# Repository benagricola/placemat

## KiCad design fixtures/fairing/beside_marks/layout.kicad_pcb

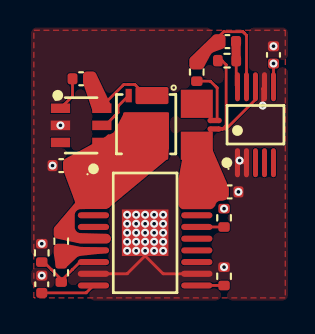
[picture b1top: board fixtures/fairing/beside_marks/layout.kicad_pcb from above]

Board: 6 copper layers, 20 parts (0 on the bottom side), 17 nets.

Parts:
C1: CL05B103KB5NNNC; C_0402_1005Metric
C2, C3, C4, C5, C6: CL05B104KB54PNC; C_0402_1005Metric
NT1, NT2: NetTie-2_SMD_Pad0.3mm
R1, R7: ERJ-2RKF1003X; R_0402_1005Metric
R2: ERJ-2RKF2003X; R_0402_1005Metric
R3: AC0402FR-071M2L; R_0402_1005Metric
R4: ERJ-2RKF4701X; R_0402_1005Metric
R5, R6: ERJ-2RKF10R0X; R_0402_1005Metric
R8: PE1206DRM470R01L; PE1206_Yageo_Table8
U1: TPS16630PWPR; HTSSOP-20_L6.5-W4.4-P0.65-LS6.4-TL-EP2.58
U2: INA226AIDGSR; MSOP-10_L3.0-W3.0-P0.50-LS5.0-BL
U3: MDDG06R10Q; DFN-8_L3.3-W3.3-P0.65-BL
U4: LM74700QDBVRQ1; SOT-23-6_L2.9-W1.6-P0.95-LS2.8-TL

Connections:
DVDT_SET: C1.1, U1.10
GND: C1.2, C3.2, C5.2, C6.2, R1.2, R4.2, U1.9, U1.12, U1.21, U2.1, U2.2, U2.7, U4.2
ILIM_SET: R4.1, U1.11
INA_N: C2.2, R5.2, U2.9
INA_P: C2.1, R6.2, U2.10
OVP_SET: R1.1, R2.2, U1.8
PGOOD: R7.2, U1.16
REV_CAP: C4.1, U4.1
REV_GATE: U3.4, U4.5
UVLO_SET: R2.1, R3.2, U1.7
V3V3: C3.1, R7.1, U2.6
VBIKE: C4.2, U3.1, U3.2, U3.3, U4.6
VPROT: C5.1, NT1.1, R8.1, U1.18, U1.19, U1.20
VPROT_IN: C6.1, R3.1, U1.1, U1.2, U1.3, U1.6, U3.5, U4.4
VPROT_SENSE: NT1.2, R6.1, U2.8
VSHUNT: NT2.1, R8.2
VSHUNT_SENSE: NT2.2, R5.1

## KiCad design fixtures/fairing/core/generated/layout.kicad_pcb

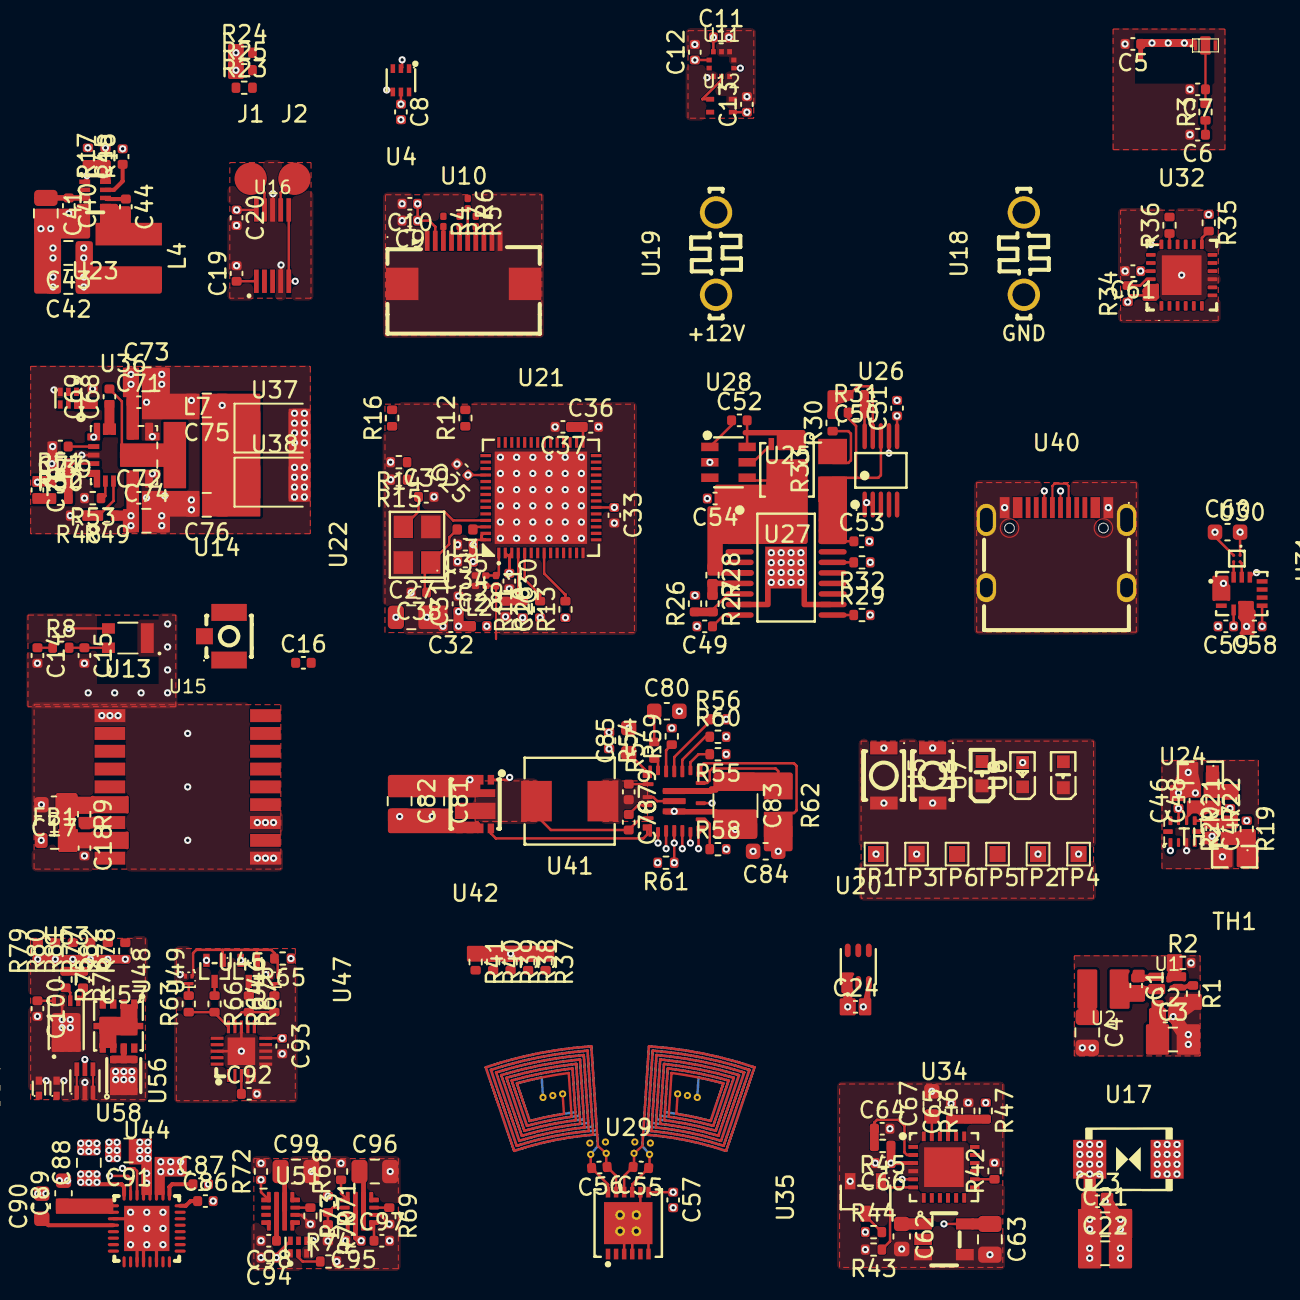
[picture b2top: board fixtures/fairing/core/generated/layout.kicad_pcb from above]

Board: 6 copper layers, 258 parts (0 on the bottom side), 154 nets.

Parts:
C1, C2, C8, C9, C11, C12, C13, C16, C18, C23, C25, C30, C32, C33, C37, C40, C44, C46, C47, C48, C50, C51, C52, C53, C54, C58, C59, C61, C65, C66, C68, C69, C71, C72, C78, C79, C92, C93, C94, C95, C98, C100: CL05B104KB54PNC; C_0402_1005Metric
C3, C4, C21, C22, C27, C41, C63, C81, C82, C88, C91: GRM21BR61H106KE43L; C_0805_2012Metric
C5, C6, C7: GRM1555C1H1R0BA01D; C_0402_1005Metric
C10, C24, C26, C31, C34, C36, C57, C77: CL05A105KA5NQNC; C_0402_1005Metric
C14, C15: GCM1555C1H100FA16D; C_0402_1005Metric
C17, C85, C89, C90: CL10A106MA8NRNC; C_0603_1608Metric
C19, C20: KAM05CR71A105MH; C_0402_1005Metric
C28, C29: GRM0335C1H1R5CA01D; C_0201_0603Metric
C35, C49, C64, C97: CL05B103KB5NNNC; C_0402_1005Metric
C38, C39: GCM1555C1H160FA16D; C_0402_1005Metric
C42, C43, C75, C76: GRM21BZ71A226ME15L; C_0805_2012Metric
C45: GRM155R71H333KE14D; C_0402_1005Metric
C55, C56, C86, C87: CL05C331JB5NNNC; C_0402_1005Metric
C60, C84: GRM188R61E475KE11D; C_0603_1608Metric
C62: CL10A105KB8NNNC; C_0603_1608Metric
C67: CL10B474KA8NNNC; C_0603_1608Metric
C70: GCM1555C1H220FA16D; C_0402_1005Metric
C73, C74: CL21A475KBQNNNE; C_0805_2012Metric
C80: 0603B222K500NT; C_0603_1608Metric
C83: GMK325BJ226MM-T; C_1210_3225Metric
C96, C99: CL21A225KBQNNNE; C_0805_2012Metric
FB1: BLM18EG601SZ1D; R_0603_1608Metric
J1, J2: YTC1P-3515-01; TESTPOINT-SMD_BD2.0_pitch2.7
L1: 2.4nH; L_0201_0603Metric
L2: LQG15HS2N0S02D; L_0402_1005Metric
L3: 24nH; L_0402_1005Metric
L4: APH404012C2R2MP01; APH404012_APV_land
L5: PCB sector coil V3; RingCoil_V3_M
L6: PCB sector coil V3; RingCoil_V3
L7: APH404012C1R5MP01; APH404012_APV_land
R1, R24, R25, R29, R40, R41: ERJ-2RKF4701X; R_0402_1005Metric
R2: WR04W2R00FTL; R_0402_1005Metric
R3, R8, R9, R54, R60: ERJ-2GE0R00X; R_0402_1005Metric
R4, R5, R6, R7: RC0201FR-0733RL; R_0201_0603Metric
R10, R11, R13, R14, R15, R17, R23, R34, R35, R37, R57, R58, R75, R76, R77, R78, R79, R80, R81, R82: 0402WGF1002TCE; R_0402_1005Metric
R12: ERJ-2RKF1000X; R_0402_1005Metric
R16: 0402WGF5100TCE; R_0402_1005Metric
R18: ERJ-2RKF3162X; R_0402_1005Metric
R19, R21, R45: ERJ-2RKF4702X; R_0402_1005Metric
R20, R22, R36, R52: ERJ-2RKF1001X; R_0402_1005Metric
R26, R32, R38, R39, R42, R46, R49, R55, R56, R61, R65, R66, R67, R68, R70, R72, R74: ERJ-2RKF1003X; R_0402_1005Metric
R27: ERJ-2RKF2003X; R_0402_1005Metric
R28: AC0402FR-071M2L; R_0402_1005Metric
R30, R31: ERJ-2RKF10R0X; R_0402_1005Metric
R33, R62: PE1206DRM470R01L; PE1206_Yageo_Table8
R43, R44, R47, R63, R64: ERJ-2RKF1004X; R_0402_1005Metric
R48: ERJ-2RKF2212X; R_0402_1005Metric
R50: RT0402BRD0716K9L; R_0402_1005Metric
R51: RT0402BRD0769K8L; R_0402_1005Metric
R53: ERJ-2RKF5761X; R_0402_1005Metric
R59: ERJ-2RKF5102X; R_0402_1005Metric
R69: ERJ-2RKF6651X; R_0402_1005Metric
R71: 400k; R_0402_1005Metric
R73: ERJ-2RKF9760X; R_0402_1005Metric
TH1, TH2: NCU18XH103F60RB; R0603
TP1, TP2, TP3, TP4, TP5, TP6: ?; TestPoint_Pad_1.0x1.0mm
U1: TPS92200D2RXLR; RXL0006A_TI_land
U2: DFE252012F-2R2M=P2; DFE252012F_Murata_land
U3: ANT016008LCS2442MA1; ANT-SMD_6P-L1.6-W0.8-P1.20-1
U4: TMP102AIDRLR(UMW); SOT-563_L1.6-W1.2-P0.50-LS1.6-BL
U5: KT-0603R; LED-SMD_L1.6-W0.8-R-RD
U6: KT-0603W; LED0603-R-RD_WHITE
U7: KT-0603YG; LED0603-RD
U8, U9: B3U-1000P; KEY-SMD_B3U-1000PM
U10: 05A20L10P; FPC-SMD_10P-P0.50_05A20L10P
U11: BMP581; BMP581_Bosch_land
U12: SHT40-AD1B-R3; SHT40_Sensirion_land
U13: W3011; ANT-W3011_DATASHEET
U14: BWU.FL-IPEX1; IPEX-SMD_BWIPX-1-001E
U15: MAX-M10S-00B; GNSS_LCC18_shared_land
U16: DRV2605LDGSR; DGS0010A_TI_land
U17: SMBJ26CA; SMB_L4.6-W3.6-LS5.3-BI
U18, U19: 1217169-1; TH-2P_L7.9-W0.80-P5.08
U20: LTR-303ALS-01; TDFN-6_L2.0-W2.0-P0.65-BL
U21: ESP32-S3FH4R2; QFN-56_L7.0-W7.0-P0.40-BL-EP5.7
U22: S3240000101040; CRYSTAL-SMD_4P-L3_2-W2_5-BL
U23: TPS62933DRLR; SOT-583-8_L2.1-W1.2-P0.50-LS1.6-BR
U24: ADS1115IRUGR; ADS1115_RUG0010A
U25: TPS16630PWPR; HTSSOP-20_L6.5-W4.4-P0.65-LS6.4-TL-EP2.58
U26: INA226AIDGSR; MSOP-10_L3.0-W3.0-P0.50-LS5.0-BL
U27: MDDG06R10Q; DFN-8_L3.3-W3.3-P0.65-BL
U28: LM74700QDBVRQ1; SOT-23-6_L2.9-W1.6-P0.95-LS2.8-TL
U29: LDC1612DNTR; WSON-12_L4_0-W4_0-P0_50-BL-EP
U30: LSM6DS3TR-C; LGA-14_L3.0-W2.5-P0.50-TL
U31: MMC5603NJ; FLIPCHIP-4_L0.8-W0.8-R2-C2-P0.40-TL
U32: TCA9555RTWR; VFQFPN-24_L4.0-W4.0-P0.50-BL-EP2.8
U33: TPS7B6933DBVR; TSOT-23-5_L2.9-W1.6-P0.95-LS2.8-BR
U34: MSPM0L1106TRGER; VQFN-24_L4.0-W4.0-P0.50-TL-EP2.5
U35: 2N7002; SOT-23-3_L2.9-W1.3-P1.90-LS2.4-BR
U36: LM61440AASQRJRRQ1; VQFN-14_L4.0-W3.5-P0.5-BL-RJR0014A
U37, U38: T520T107M006APE070; CP_EIA-3528-12_Kemet-T
U39: SN74LVC1G07DRYR(UMW); SON-6_L1.5-W1.0-P0.50-BL
U40: TYPE-C-31-M-12; TYPE-C-31-M-12-corrected-power-lands
U41: MWSA0518S-2R2MT; IND-SMD_L5.4-W5.2
U42: AON7934; DFN-8_L3.0-W3.0-P0.65-BL_AON7934
U43: TPS55288RPMR; RPM0026A
U44: TPS25751SRSMR; QFN-32_L4.0-W4.0-P0.40-TL-EP2.8
U45: TPD6S300RUKR; WQFN-20_L3.0-W3.0-P0.40-BL-EP1.7
U46, U47: CSD15380F3; PICOSTAR-3_L0.7-W0.6-P0.35-TL
U48, U49: DMG1013T-7; SC-75-3_L1.6-W0.8-P1.00-LS1.6-BR
U50, U52: TPS259470LRPWR; RPW0010A
U51: SN74LVC1G08DRYR; SON-6_L1.5-W1.0-P0.50-BL
U53: M24512-DFMC6TG; DFN-8_L3.0-W2.0-P0.50-BL-EP
U54, U55: ESD9B5.0ST5G; SOD-923_L0.8-W0.6-LS1.0-BI
U56: USBLC6-2P6; SOT-666-6_L1.6-W1.2-P0.50-LS1.6-BR
U57: TVS2200DRVR; WSON-6_L2.0-W2.0-P0.65-BL-EP
U58: AON7804; DFN-8_L3.0-W3.0-P0.65-BL_AON7804-1

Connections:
ALS_INT: R37.2, U20.5, U32.14
BB_FAULT: R35.2, R55.2, U32.13, U43.14
BL_LEDK: R2.1, U1.6, U10.9
BL_PWM: R1.1, U1.5, U21.10
BOOT_STRAP: R10.2, TP2.1, U8.1, U21.5
DISP_CS: R4.1, U21.17
DISP_DC: R5.1, U21.22
DISP_MOSI: R6.1, U21.21
DISP_RST: U10.4, U21.18
DISP_SCK: R7.1, U21.19
DISP_TE: U10.8, U21.23
EFUSE_SHDN: U25.13, U34.5
GND: C2.2, C3.2, C4.2, C5.2, C6.2, C7.2, C8.2, C9.2, C10.2, C11.2, C12.2, C13.2, C14.2, C15.2, C16.2, C17.2, C18.2, C19.2, C20.2, C21.2, C22.2, C23.2, C24.2, C25.2, C26.2, C27.2, C28.2, C29.2, C30.2, C31.2, C32.2, C33.2, C34.2, C35.2, C36.2, C37.2, C38.2, C39.2, C40.2, C41.2, C42.2, C43.2, C45.2, C46.2, C47.2, C48.2, C49.2, C51.2, C53.2, C54.2, C57.2, C58.2, C59.2, C60.2, C61.2, C62.2, C63.2, C64.2, C65.2, C66.2, C67.2, C69.2, C71.2, C72.2, C73.2, C74.2, C75.2, C76.2, C77.2, C81.2, C82.2, C83.2, C84.2, C86.2, C87.2, C88.2, C89.2, C90.2, C91.2, C92.2, C93.2, C94.2, C95.2, C96.2, C97.2, C98.2, C99.2, C100.2, R1.2, R2.2, R14.2, R15.2, R17.2, R26.2, R29.2, R42.2, R43.2, R46.2, R48.2, R50.2, R53.2, R54.2, R58.2, R61.2, R68.2, R69.2, R70.2, R72.2, R73.2, R74.2, TH1.2, TH2.2, TP3.1, U1.4, U3.4, U4.2, U4.4, U5.2, U6.2, U8.2, U9.2, U10.10, U10.11, U10.12, U11.3, U11.5, U11.7, U11.8, U11.9, U12.4, U13.2, U14.2, U14.3, U15.1, U15.10, U15.12, U16.4, U16.8, U17.2, U18.1, U18.2, U20.3, U21.57, U22.2, U22.4, U23.1, U23.4, U24.3, U25.9, U25.12, U25.21, U26.1, U26.2, U26.7, U28.2, U29.3, U29.4, U29.6, U29.8, U29.13, U30.1, U30.2, U30.3, U30.6, U30.7, U31.A1, U32.9, U32.25, U33.3, U33.4, U34.4, U34.25, U35.2, U36.3, U36.9, U36.11, U37.2, U38.2, U39.3, U40.1, U40.2, U40.3, U40.4, U40.A1B12, U40.B1A12, U42.5, U42.6, U42.7, U43.7, U43.9, U43.24, U44.3, U44.11, U44.12, U44.14, U44.33, U45.4, U45.5, U45.6, U45.7, U45.8, U45.13, U45.18, U45.21, U46.2, U47.2, U50.8, U51.3, U52.8, U53.1, U53.2, U53.3, U53.4, U53.7, U53.9, U54.2, U55.2, U56.2, U57.1, U57.2, U57.3, U57.7
GNSS_PPS: U15.4, U21.9
GNSS_RX: U15.3, U21.7
GNSS_TX: U15.2, U21.6
IMU_INT1: U21.27, U30.4
INA_ALERT: R34.2, R38.2, U21.12, U26.3, U32.22
LED_BIKE: R23.2, U5.1
LED_STATUS: R12.2, U6.1
LED_USB_K: R36.2, U7.1
MCU_EN: C26.1, R11.2, TP4.1, U9.1, U21.4
PD_IRQ: R78.2, U21.47, U44.10
PD_NEGOTIATING: R77.2, U21.44, U44.13
PD_PDO0: R79.2, U21.11, U44.6
PD_PDO1: R80.2, U21.16, U44.7
PD_PDO2: R81.2, U21.24, U44.18
PGOOD: R32.2, U25.16, U32.12
PP5V: C70.1, C75.1, C76.1, C91.1, L7.2, R51.1, U36.1, U37.1, U38.1, U44.28, U44.29
RAIL_FAULT: R39.2, U25.15, U32.15
REV_EN: R44.2, U28.3, U35.3
RF_50: C6.1, C28.1, L1.2, R3.1
RING_INT: U21.15, U29.5
SCL: R40.2, U11.2, U12.2, U16.2, U20.4, U21.14, U29.1, U30.13, U31.A2, U34.1
SCL_PWR: R24.2, U4.1, U21.37, U24.10, U26.5, U32.19, U43.5, U44.9
SDA: R41.2, U11.4, U12.1, U16.3, U20.6, U21.13, U29.2, U30.14, U31.B2, U34.24
SDA_PWR: R25.2, U4.6, U21.48, U24.9, U26.4, U32.20, U43.6, U44.8
UART_RX: TP5.1, U21.50
UART_TX: R16.2, TP6.1
USB_CC1: C86.1, U40.A5, U44.24, U54.1
USB_CC2: C87.1, U40.B5, U44.25, U55.1
USB_D_N: U21.25, U40.A7, U40.B7, U56.3, U56.4
USB_D_P: U21.26, U40.A6, U40.B6, U56.1, U56.6
USB_HV: C84.1, C98.1, R62.2, U43.13, U52.5
USB_SBU1: U40.A8, U45.1
USB_SBU2: U40.B8, U45.2
USB_WET: R82.2, U21.45, U44.30, U52.2
V3V3: C8.1, C9.1, C10.1, C11.1, C12.1, C13.1, C20.1, C24.1, C25.1, C27.1, C31.1, C32.1, C33.1, C34.1, C35.1, C42.1, C43.1, C46.1, C51.1, C57.1, C58.1, C59.1, C60.1, C61.1, C69.1, C88.1, C94.1, FB1.1, L2.1, L4.2, R10.1, R11.1, R13.1, R18.1, R19.1, R21.1, R24.1, R25.1, R32.1, R34.1, R35.1, R37.1, R38.1, R39.1, R40.1, R41.1, R55.1, R77.1, R78.1, R79.1, R80.1, R81.1, R82.1, TP1.1, U4.5, U7.2, U10.2, U11.1, U11.6, U11.10, U12.3, U16.5, U16.6, U16.10, U20.1, U21.20, U21.46, U21.55, U21.56, U24.1, U24.8, U26.6, U29.7, U30.5, U30.8, U30.12, U31.B1, U32.18, U32.21, U32.23, U32.24, U39.6, U44.32, U51.6, U56.5
VBIKE: C21.1, C22.1, C23.1, C52.2, R44.1, R47.1, U17.1, U19.1, U19.2, U27.1, U27.2, U27.3, U28.6
VBUS: C99.1, U40.A4B9, U40.B4A9, U44.26, U44.27, U52.6, U57.4, U57.5, U57.6, U58.5
VBUS_EN: R61.1, U21.36, U39.2, U43.4, U51.1
VLED: C4.1, U2.2, U10.1
VPROT_IN: C54.1, C62.1, R28.1, U25.1, U25.2, U25.3, U25.6, U27.5, U28.4, U33.1
VSHUNT: C2.1, C3.1, C40.1, C41.1, C71.1, C72.1, C73.1, C74.1, C81.1, C82.1, C96.1, R23.1, R30.1, R33.2, R49.1, U1.3, U23.3, U36.8, U36.12, U42.2, U42.3, U42.4, U42.9, U43.3, U50.6
backlight.BL_BOOT: C1.1, U1.1
backlight.SW_BL: C1.2, U1.2, U2.1
ble.ANT24_FEED: C7.1, R3.2, U3.2, U3.3, U3.5, U3.6
ble.ANT24_RAD: C5.1, U3.1
display.DISP_CS_P: R4.2, U10.3
display.DISP_DC_P: R5.2, U10.7
display.DISP_MOSI_P: R6.2, U10.6
display.DISP_SCK_P: R7.2, U10.5
gnss.ANT_FEED: C14.1, R8.1, U14.1, U15.11
gnss.GNSS_VCC: C17.1, C18.1, FB1.2, R9.1, U15.6, U15.8
gnss.GNSS_VCC_RF: C16.1, U15.14
gnss.GNSS_VIO: R9.2, U15.7
gnss.ant_rf.ANT_TRACE: C15.1, R8.2, U13.1
haptics.HAPTIC_REG: C19.1, U16.1
haptics.LRA_N: J1.1, U16.9
haptics.LRA_P: J2.1, U16.7
logic.LED_STATUS_DRIVE: R12.1, U21.43
logic.RF_CHIP: C29.1, L1.1, U21.1
logic.STRAP_DOWNLOAD: R15.1, U21.52
logic.STRAP_JTAG: R13.2, U21.8
logic.STRAP_VSPI: R14.1, U21.51
logic.UART_TX_CHIP: R16.1, U21.49
logic.VDD_RF: C30.1, L2.2, U21.2, U21.3
logic.VDD_SPI: C36.1, C37.1, U21.29
logic.XTAL_1: C38.1, L3.2, U22.1
logic.XTAL_N: C39.1, U21.53, U22.3
logic.XTAL_P: L3.1, U21.54
logicsupply.BST_3V3: C44.1, U23.6
logicsupply.FB_3V3: R17.1, R18.2, U23.8
logicsupply.SS_3V3: C45.1, U23.7
logicsupply.SW_3V3: C44.2, L4.1, U23.5
monitoring.ADC_BUCK: C47.1, R20.2, U24.6
monitoring.ADC_PD: C48.1, R22.2, U24.7
monitoring.NTC_BUCK: R19.2, R20.1, TH1.1
monitoring.NTC_PD: R21.2, R22.1, TH2.1
protect.DVDT_SET: C49.1, U25.10
protect.ILIM_SET: R29.1, U25.11
protect.INA_N: C50.2, R30.2, U26.9
protect.INA_P: C50.1, R31.2, U26.10
protect.OVP_SET: R26.1, R27.2, U25.8
protect.REV_CAP: C52.1, U28.1
protect.REV_GATE: U27.4, U28.5
protect.UVLO_SET: R27.1, R28.2, U25.7
protect.VPROT: C53.1, R31.1, R33.1, U25.18, U25.19, U25.20, U26.8
ring.COIL0_A: C55.1, L5.2, U29.9
ring.COIL0_B: C55.2, L5.1, U29.10
ring.COIL1_A: C56.1, L6.1, U29.11
ring.COIL1_B: C56.2, L6.2, U29.12
status.LED_USB_SINK: R36.1, U32.17
supervisor.REV_EN_GATE: R43.1, U34.6, U35.1
supervisor.SUP_BSL: R42.1, U34.14
supervisor.SUP_NRST: C64.1, R45.2, U34.2
supervisor.SUP_VCORE: C67.1, U34.23
supervisor.VIN_SENSE: C65.1, R46.1, R47.2, U34.21
supervisor.V_AON: C63.1, C66.1, R45.1, U33.5, U34.3
usb5v.BST_5V: C68.1, U36.13, U36.14
usb5v.EN_5V: R48.1, R49.2, U36.7, U39.4
usb5v.FB_5V: R50.1, R51.2, R52.2, U36.4
usb5v.FF_5V: C70.2, R52.1
usb5v.RT_5V: R53.1, U36.6
usb5v.SW_5V: C68.2, L7.1, U36.10
usb5v.VCC_5V: C77.1, U36.2
usbconverter.AGND: C80.2, C85.2, R54.1, R56.2, R59.2, R60.2, U43.10
usbconverter.BOOT1: C78.1, U43.22
usbconverter.BOOT2: C79.1, U43.20
usbconverter.CDC_SET: R56.1, U43.16
usbconverter.COMP_BB: R57.1, U43.18
usbconverter.COMP_MID: C80.1, R57.2
usbconverter.DR1H: U42.1, U43.2
usbconverter.DR1L: U42.8, U43.1
usbconverter.FSW_SET: R58.1, U43.8
usbconverter.ILIM_BB: R59.1, U43.17
usbconverter.ISP: C83.1, R62.1, U43.11, U43.12, U43.26
usbconverter.MODE_BB: R60.1, U43.15
usbconverter.SW1: C78.2, U41.1, U42.10, U43.23
usbconverter.SW2: C79.2, U41.2, U43.21, U43.25
usbconverter.VCC_BB: C85.1, U43.19
usbpd.EXCITE: R65.2, U44.31, U46.1, U47.1, U48.1, U49.1
usbpd.LD1: R63.1, R66.2, U44.22, U45.15
usbpd.LD2: R64.1, R67.2, U44.23, U45.14
usbpd.PC_IN: C95.1, R71.1, U44.19, U50.5, U58.2
usbpd.PD_I2CC_SCL: R75.2, U44.16, U53.6
usbpd.PD_I2CC_SDA: R76.2, U44.15, U53.5
usbpd.PD_LDO_3V3: C89.1, C93.1, C100.1, R65.1, R75.1, R76.1, U44.1, U44.2, U45.10, U48.2, U49.2, U53.8
usbpd.PD_SINK: R68.1, U44.5, U50.1
usbpd.PD_SOURCE: R74.1, U44.17, U51.2
usbpd.SINK_GATE_VBUS: U44.21, U58.6
usbpd.SINK_GATE_VSYS: U44.20, U58.3
usbpd.controller.PD_LDO_1V5: C90.1, U44.4
usbpd.moisture.DOWN1: R63.2, U46.3
usbpd.moisture.DOWN2: R64.2, U47.3
usbpd.moisture.PULL1: R66.1, U48.3
usbpd.moisture.PULL2: R67.1, U49.3
usbpd.moisture.SBU_BIAS: C92.1, U45.3
usbpd.paths.SINK_LIMIT: R69.1, U50.9
usbpd.paths.SINK_OVLO: R70.1, R71.2, U50.2
usbpd.paths.SINK_SLEW: C97.1, U50.7
usbpd.paths.SOURCE_EN: R72.1, U51.4, U52.1
usbpd.paths.SOURCE_LIMIT: R73.1, U52.9
usbpd.support.SINK_MID: U58.1, U58.4

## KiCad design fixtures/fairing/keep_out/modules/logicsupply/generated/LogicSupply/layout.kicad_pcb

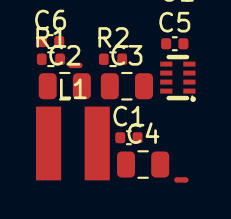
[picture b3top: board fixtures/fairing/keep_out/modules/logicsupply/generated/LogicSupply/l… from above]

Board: 6 copper layers, 12 parts (0 on the bottom side), 9 nets, no tracks yet.

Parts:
C1, C5: CL05B104KB54PNC; C_0402_1005Metric
C2: GRM21BR61H106KE43L; C_0805_2012Metric
C3, C4: GRM21BZ71A226ME15L; C_0805_2012Metric
C6: GRM155R71H333KE14D; C_0402_1005Metric
L1: APH404012C2R2MP01; APH404012_APV_land
NT1, NT2: NetTie-2_SMD_Pad0.3mm
R1: 0402WGF1002TCE; R_0402_1005Metric
R2: ERJ-2RKF3162X; R_0402_1005Metric
U1: TPS62933DRLR; SOT-583-8_L2.1-W1.2-P0.50-LS1.6-BR

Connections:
BST_3V3: C5.1, U1.6
FB_3V3: R1.1, R2.2, U1.8
FB_3V3_GND: NT1.2, R1.2
GND: C1.2, C2.2, C3.2, C4.2, C6.2, NT1.1, U1.1, U1.4
SS_3V3: C6.1, U1.7
SW_3V3: C5.2, L1.1, U1.5
V3V3: C3.1, C4.1, L1.2, NT2.1
V3V3_SENSE: NT2.2, R2.1
VSHUNT: C1.1, C2.1, U1.3

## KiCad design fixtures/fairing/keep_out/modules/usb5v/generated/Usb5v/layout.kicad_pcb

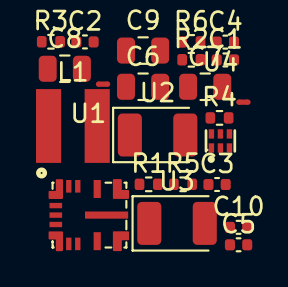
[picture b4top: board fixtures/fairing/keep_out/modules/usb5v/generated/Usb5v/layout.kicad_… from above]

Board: 6 copper layers, 23 parts (0 on the bottom side), 13 nets, no tracks yet.

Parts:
C1, C2, C4, C5: CL05B104KB54PNC; C_0402_1005Metric
C3: GCM1555C1H220FA16D; C_0402_1005Metric
C6, C7: CL21A475KBQNNNE; C_0805_2012Metric
C8, C9: GRM21BZ71A226ME15L; C_0805_2012Metric
C10: CL05A105KA5NQNC; C_0402_1005Metric
L1: APH404012C1R5MP01; APH404012_APV_land
NT1, NT2: NetTie-2_SMD_Pad0.3mm
R1: ERJ-2RKF2212X; R_0402_1005Metric
R2: ERJ-2RKF1003X; R_0402_1005Metric
R3: RT0402BRD0716K9L; R_0402_1005Metric
R4: RT0402BRD0769K8L; R_0402_1005Metric
R5: ERJ-2RKF1001X; R_0402_1005Metric
R6: ERJ-2RKF5761X; R_0402_1005Metric
U1: LM61440AASQRJRRQ1; VQFN-14_L4.0-W3.5-P0.5-BL-RJR0014A
U2, U3: T520T107M006APE070; CP_EIA-3528-12_Kemet-T
U4: SN74LVC1G07DRYR(UMW); SON-6_L1.5-W1.0-P0.50-BL

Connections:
BST_5V: C1.1, U1.13, U1.14
EN_5V: R1.1, R2.2, U1.7, U4.4
FB_5V: R3.1, R4.2, R5.2, U1.4
FB_5V_GND: NT1.2, R3.2
FF_5V: C3.2, R5.1
GND: C2.2, C4.2, C5.2, C6.2, C7.2, C8.2, C9.2, C10.2, NT1.1, R1.2, R6.2, U1.3, U1.9, U1.11, U2.2, U3.2, U4.3
PP5V: C8.1, C9.1, L1.2, NT2.1, U2.1, U3.1
PP5V_SENSE: C3.1, NT2.2, R4.1, U1.1
RT_5V: R6.1, U1.6
SW_5V: C1.2, L1.1, U1.10
V3V3: C2.1, U4.6
VCC_5V: C10.1, U1.2
VSHUNT: C4.1, C5.1, C6.1, C7.1, R2.1, U1.8, U1.12

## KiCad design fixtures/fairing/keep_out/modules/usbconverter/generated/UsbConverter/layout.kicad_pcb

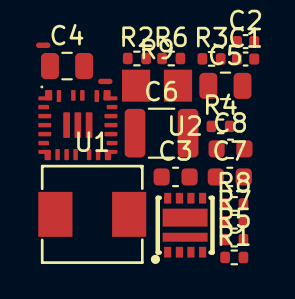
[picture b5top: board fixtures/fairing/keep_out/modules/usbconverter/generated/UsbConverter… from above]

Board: 6 copper layers, 22 parts (0 on the bottom side), 22 nets, no tracks yet.

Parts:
C1, C2: CL05B104KB54PNC; C_0402_1005Metric
C3: 0603B222K500NT; C_0603_1608Metric
C4, C5: GRM21BR61H106KE43L; C_0805_2012Metric
C6: GMK325BJ226MM-T; C_1210_3225Metric
C7: GRM188C81E475ME11D; C_0603_1608Metric
C8: CL10A106MA8NRNC; C_0603_1608Metric
NT1, NT2: NetTie-2_SMD_Pad0.3mm
R1, R7: ERJ-2GE0R00X; R_0402_1005Metric
R2, R3, R8: ERJ-2RKF1003X; R_0402_1005Metric
R4, R5: 0402WGF1002TCE; R_0402_1005Metric
R6: ERJ-2RKF5102X; R_0402_1005Metric
R9: PE1206DRM470R01L; PE1206_Yageo_Table8
U1: MWSA0518S-2R2MT; IND-SMD_L5.4-W5.2
U2: AON7934; DFN-8_L3.0-W3.0-P0.65-BL_AON7934
U3: TPS55288RPMR; RPM0026A

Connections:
AGND: C3.2, C8.2, R1.1, R3.2, R5.2, R6.2, R7.2, U3.7, U3.10
BB_FAULT: R2.2, U3.14
BOOT1: C1.1, U3.22
BOOT2: C2.1, U3.20
CDC_SET: R3.1, U3.16
COMP_BB: R4.1, U3.18
COMP_MID: C3.1, R4.2
DR1H: U2.1, U3.2
DR1L: U2.8, U3.1
FSW_SET: R5.1, U3.8
GND: C4.2, C5.2, C6.2, C7.2, R1.2, R8.2, U2.5, U2.6, U2.7, U3.9, U3.24
ILIM_BB: R6.1, U3.17
ISN: NT1.2, U3.13
ISP: NT2.2, U3.12
MODE_BB: R7.1, U3.15
SW1: C1.2, U1.1, U2.10, U3.23
SW2: C2.2, U1.2, U3.21, U3.25
VBUS: C7.1, NT1.1, R9.2
VBUS_EN: R8.1, U3.4
VCC_BB: C8.1, U3.19
VOUT: C6.1, NT2.1, R9.1, U3.11, U3.26
VSHUNT: C4.1, C5.1, U2.2, U2.3, U2.4, U2.9, U3.3

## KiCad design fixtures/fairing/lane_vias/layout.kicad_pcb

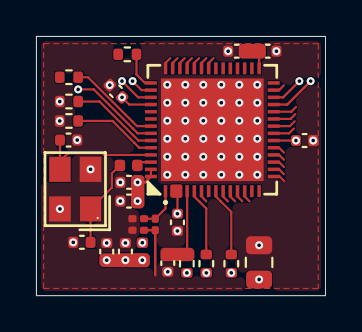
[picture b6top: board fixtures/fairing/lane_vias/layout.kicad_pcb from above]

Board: 6 copper layers, 16.1 x 14.4 mm, 27 parts (0 on the bottom side), 16 nets.

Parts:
C1, C2, C6, C7, C8, C9, C10, C11, C12, C13, C14, C15: C; C_0402_1005Metric
C3: C; C_0805_2012Metric
C4, C5: C; C_0201_0603Metric
L1: L; L_0201_0603Metric
L2, L3: L; L_0402_1005Metric
R1, R2, R3, R4, R5, R6, R7: R; R_0402_1005Metric
U1: U; QFN-56_L7.0-W7.0-P0.40-BL-EP5.7
U2: U; CRYSTAL-SMD_4P-L3_2-W2_5-BL

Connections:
GND: C1.2, C2.2, C3.2, C4.2, C5.2, C6.2, C7.2, C8.2, C9.2, C10.2, C11.2, C12.2, C13.2, C14.2, C15.2, R5.2, R6.2, U1.57, U2.2, U2.4
N2: C4.1, L1.2
N4: C14.1, L3.2, U2.1
P1: C5.1, L1.1, U1.1
P2: C6.1, L2.2, U1.2, U1.3
P4: C2.1, R2.2, U1.4
P5: R1.2, U1.5
P8: R4.2, U1.8
P29: C12.1, C13.1, U1.29
P43: R3.1, U1.43
P49: R7.1, U1.49
P51: R5.1, U1.51
P52: R6.1, U1.52
P53: C15.1, U1.53, U2.3
P54: L3.1, U1.54
VDD: C1.1, C3.1, C7.1, C8.1, C9.1, C10.1, C11.1, L2.1, R1.1, R2.1, R4.1, U1.20, U1.46, U1.55, U1.56
